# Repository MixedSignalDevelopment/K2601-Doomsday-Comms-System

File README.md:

# Doomsday Comms System (D.C.S.) — Customer Files

**SKU:** OS2601 · **Board revision:** rev B · © Mixed Signal Development GmbH

This package contains everything needed to review, fabricate, assemble, and
re-flash the Doomsday Comms System board — a two-unit personal LoRa text
messenger built on an nRF52840 (BLE) + SX1262 (LoRa 868 MHz) with a 128×64 mono
LCD, jog-wheel input, LRA haptics, piezo, and USB-C LiPo charging.

## Contents

| Folder | What's inside |
|--------|---------------|
| [`01_KiCad_Project/`](01_KiCad_Project/) | Editable source design — KiCad 7 schematic + PCB layout |
| [`02_Gerbers/`](02_Gerbers/) | Fabrication data — RS-274X gerbers + Excellon drills (4-layer) |
| [`03_BOM/`](03_BOM/) | Bill of materials (rev B) with MPNs and LCSC part numbers |
| [`04_3D_Model/`](04_3D_Model/) | Full assembly 3D model (STEP) for enclosure/mechanical fit |
| [`05_Firmware/`](05_Firmware/) | Source firmware (PlatformIO) — bring-up tester + messenger apps |

Each folder has its own `README.md` with the specifics.

## Ownership & licensing

- Design © 2026 **Mixed Signal Development GmbH**.
- **Firmware** is released under the **MIT License** — see
  [`05_Firmware/LICENSE`](05_Firmware/LICENSE).

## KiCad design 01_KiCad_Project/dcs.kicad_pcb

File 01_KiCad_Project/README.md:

# KiCad Project — Schematic & PCB

Editable source design for the Doomsday Comms System (D.C.S., SKU OS2601),
board rev B.

## Files

| File / folder | Description |
|---------------|-------------|
| `dcs.kicad_pro` | KiCad project file — open this one |
| `dcs.kicad_sch` | Schematic |
| `dcs.kicad_pcb` | PCB layout (4-layer) |
| `fp-lib-table` | Footprint-library table (project-relative, points at `Misc.pretty`) |
| `Misc.pretty/` | Bundled custom footprint library (`GSC1031YB`) |
| `3D/` | Bundled component 3D models referenced by the PCB |

## Requirements

- **KiCad 7.0 or newer** (the project was authored in KiCad 7).

Open `dcs.kicad_pro` in KiCad, then open the schematic and PCB editors from
the project window.

## Self-contained — no external libraries needed

This project has **no dependency on any machine-specific library path**. It opens
complete on a fresh KiCad install:

- **Footprints** are embedded directly in `dcs.kicad_pcb` (every placed footprint
  carries its full pad/graphics definition), so the layout opens, edits, and
  fabricates without any library at all.
- **Symbols** are cached in `dcs.kicad_sch`, so the schematic opens standalone
  too.
- The one **custom footprint library** the design uses (`GSC1031YB`) is bundled
  in `Misc.pretty/`, and `fp-lib-table` references it with the project-relative
  `${KIPRJMOD}/Misc.pretty` — so you can also place that part into new layouts.
- The per-part **3D models** are bundled in `3D/`; the PCB references them with
  the project-relative `${KIPRJMOD}/3D/…`, so the 3D viewer resolves them with no
  setup. (For a single complete model of the assembled board, the STEP in
  [`../04_3D_Model/`](../04_3D_Model/) is also provided.)

All original absolute local paths were removed — nothing points outside this
folder. The `.kicad_prl` (per-user GUI state) and editor history were not
included.

## Key components

nRF52840 module (Ebyte E73-2G4M08S1C) · SX1262 LoRa (Ai-Thinker Ra-01SH) ·
ST7565 128×64 LCD (GMG12864-06D) · DRV2605L LRA haptics · MCP73833 LiPo charger ·
TLV75533 LDO · TM-1011A jog wheel.

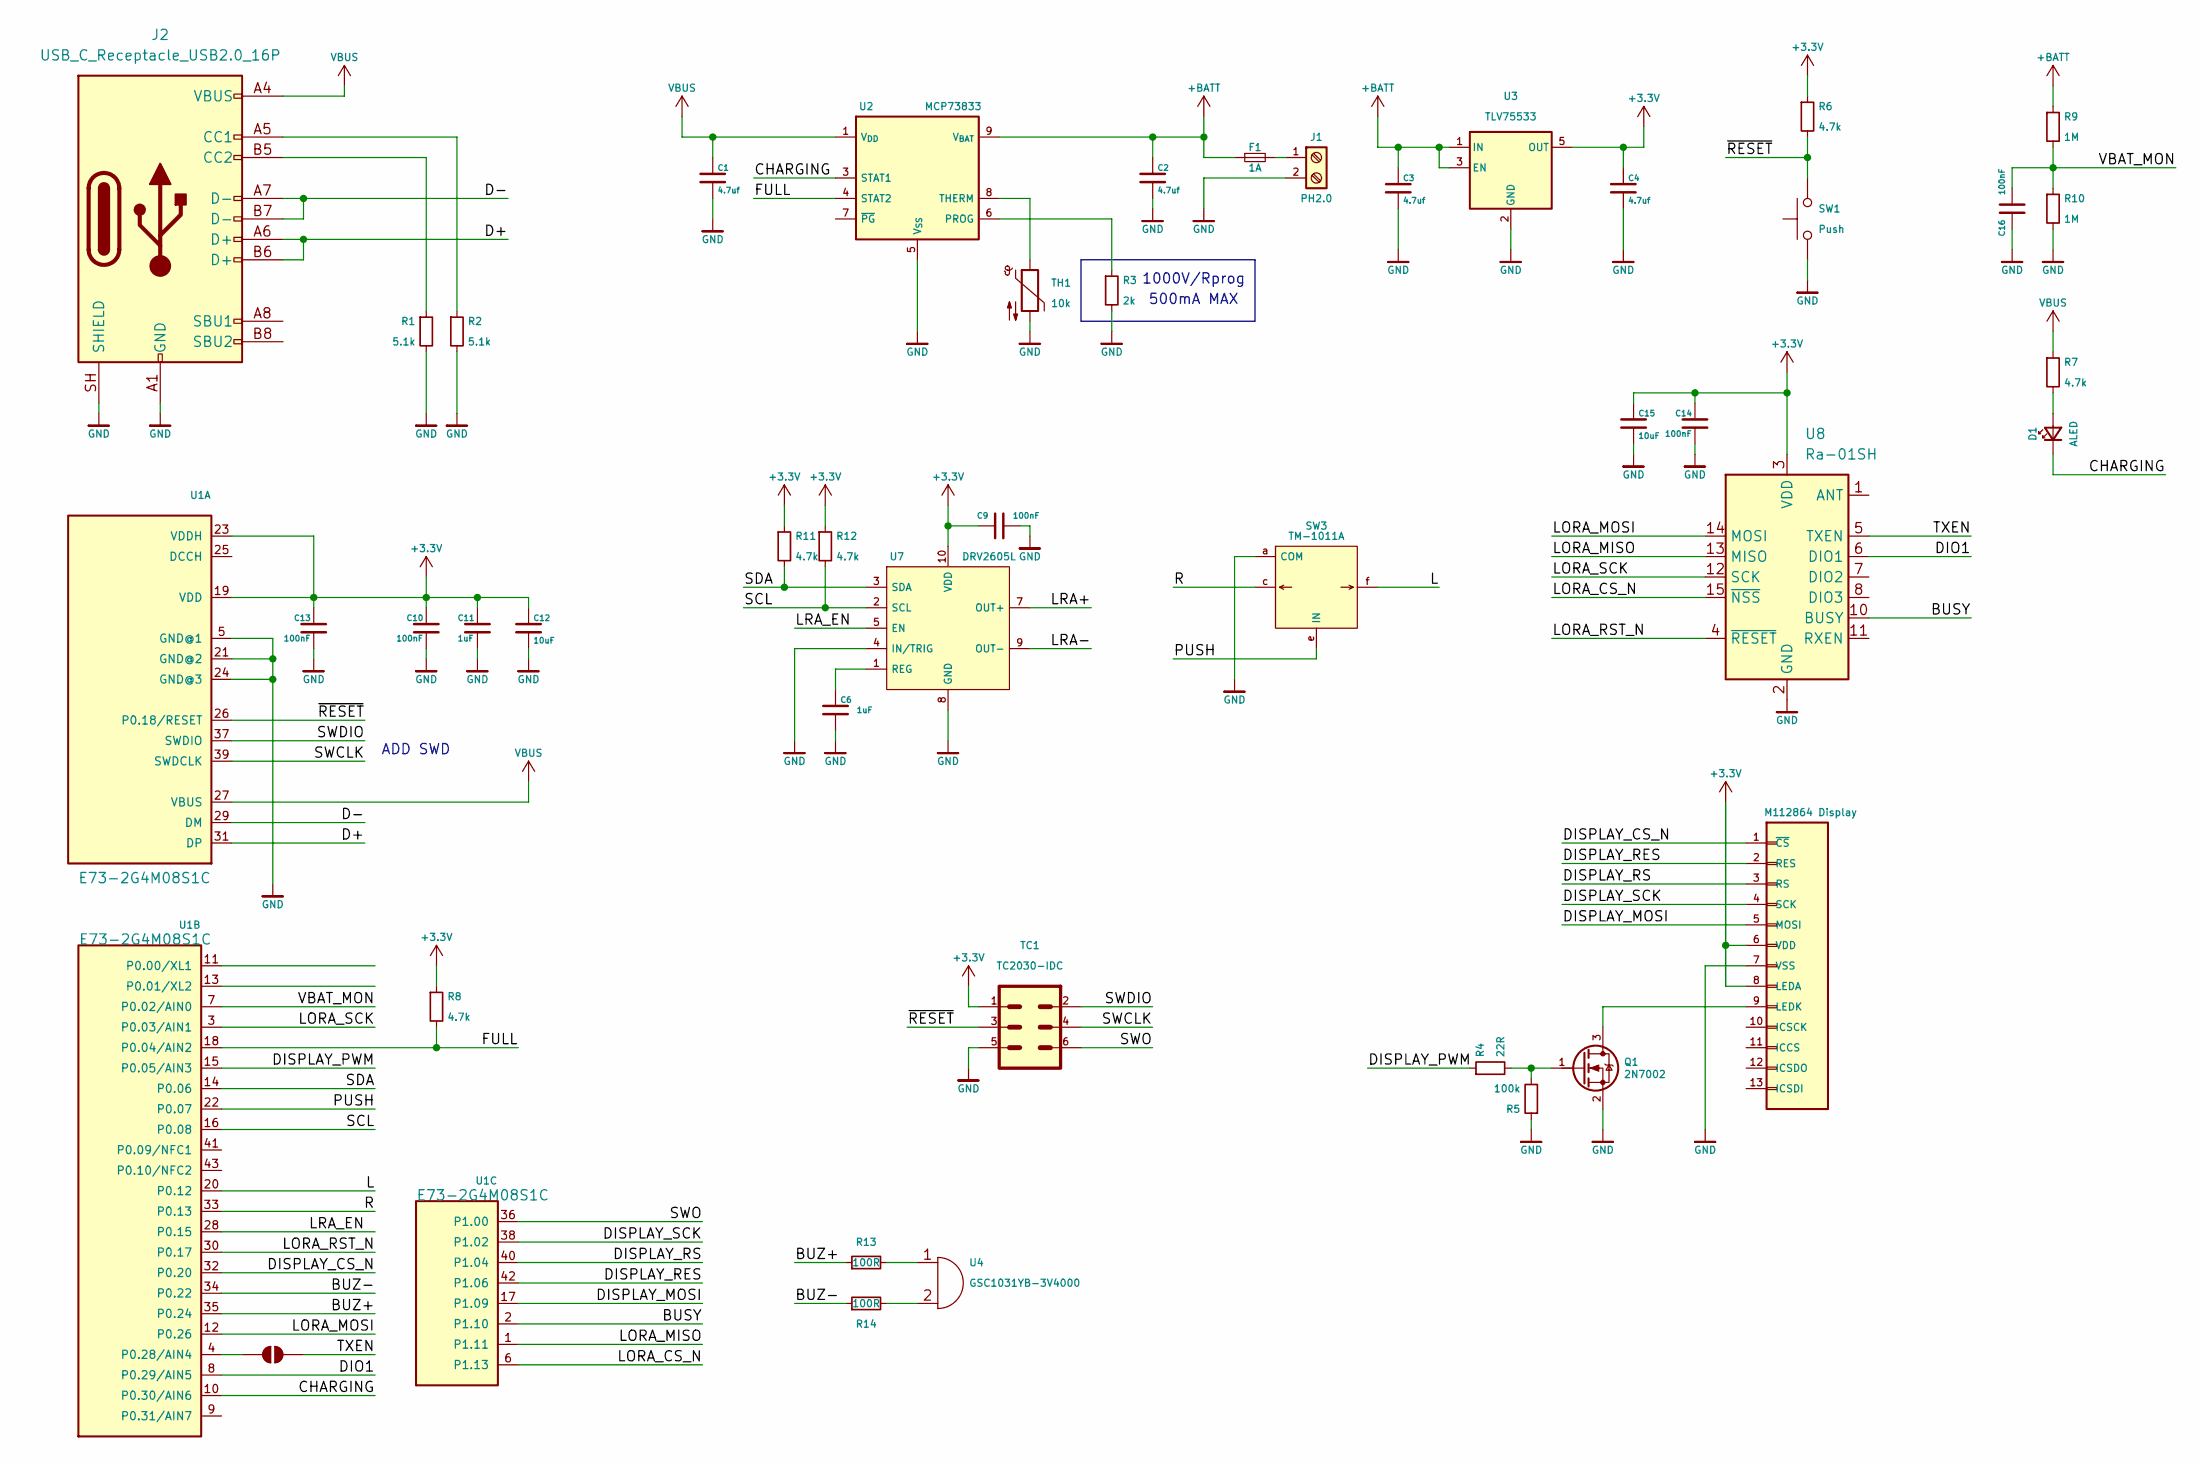
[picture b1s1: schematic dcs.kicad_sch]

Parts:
C1, C2, C3, C4: 4.7uf; C_0805; MPN CL21A475KAQNNNE; LCSC OC C354262
C6, C11: 1uF; C_0805; MPN CC0805KKX7R7BB105; LCSC OC C91186
C9, C10, C13, C14, C16: 100nF; C_0805; MPN CC0805KRX7R9BB104; LCSC OC C396718
C12, C15: 10uF; C_0805; MPN CL21B106KOQNNNE
D1: ALED; SideLED_4x1.4mm; MPN XL-4008SURC; LCSC OC C2843771
F1: 1A; R_0603; MPN JB06F1001R
J1: PH2.0; JST_PH_S2B-PH-SM4-TB_1x02-1MP_P2.00mm_Horizontal; LCSC OC C295747
J2: USB_C_Receptacle_USB2.0_16P; USB_C_16P_Horizontal; MPN TYPE-C 16PIN 2MD(073); LCSC OC C2765186
JP1: SolderJumper_2; SolderJumper-2_P1.3mm_Open_RoundedPad1.0x1.5mm
M1: 12864 Display; 12864DisplayModule
Q1: 2N7002; SOT-23; LCSC OC C916396
R1, R2: 5.1k; R_0805; MPN RC0805FR-075K1L; LCSC OC C84375
R3: 2k; R_0805; MPN RC0805JR-072KL; LCSC OC C114748
R4: 22R; R_0805; MPN RC0805FR-0722RL; LCSC OC C107702
R5: 100k; R_0805; MPN RC0805FR-07100KL; LCSC OC C96346
R6, R7, R8, R11, R12: 4.7k; R_0805; MPN RC0402FR-074K7L; LCSC OC C60816
R9, R10: 1M; R_0805; MPN RC0805FR-071ML; LCSC OC C706228
R13, R14: 100R; R_0805; MPN RC0805FR-07100RL; LCSC OC C105577
SW1: Push; SideSwitch; MPN MPTCLG-Q-T/R; LCSC OC C240296
SW3: TM-1011A; SlideKnob; MPN TM-1011A; LCSC OC C318960
TC1: TC2030-IDC
TH1: 10k; R_0603; MPN NTCG164BH103HT1; LCSC OC C415353
U1: E73-2G4M08S1C; MPN E73-2G4M08S1C; LCSC OC C356849
U2: MCP73833; MSOP-10_3x3mm_P0.5mm; MPN MCP73833T-AMI/UN
U3: TLV75533; SOT-23-5; MPN TLV75533PDYDR; LCSC OC C28642215
U4: GSC1031YB-3V4000; GSC1031YB; MPN GSC1031YB-3V4000; LCSC OC C255331
U7: DRV2605L; MSOP-10_3x3mm_P0.5mm; MPN DRV2605LDGSR; LCSC OC C527464
U8: Ra-01SH; Ai-Thinker-Ra-01-LoRa; MPN Ra-01SH; LCSC OC C2764087

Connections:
+3.3V: C4.1, C9.1, C10.1, C11.1, C12.1, C13.1, C14.1, C15.1, M1.6 (VDD), M1.8 (LEDA), R6.1, R8.1, R11.1, R12.1, TC1.1, U1.19 (VDD), U1.23 (VDDH), U3.5 (OUT), U7.6 (VDD/NC), U7.10 (VDD), U8.3 (VDD)
+BATT: C2.1, C3.1, F1.1, R9.1, U2.9 (V_{BAT}), U2.10 (V_{BAT}), U3.1 (IN), U3.3 (EN)
/BUSY: U1.2 (P1.10), U8.10 (BUSY)
/BUZ+: R13.1, U1.35 (P0.24)
/BUZ-: R14.1, U1.34 (P0.22)
/CHARGING: D1.C, U1.10 (P0.30/AIN6), U2.3 (STAT1)
/D+: J2.A6 (D+), J2.B6 (D+), U1.31 (DP)
/D-: J2.A7 (D-), J2.B7 (D-), U1.29 (DM)
/DIO1: U1.8 (P0.29/AIN5), U8.6 (DIO1)
/DISPLAY_CS_N: M1.1 (~CS), U1.32 (P0.20)
/DISPLAY_MOSI: M1.5 (MOSI), U1.17 (P1.09)
/DISPLAY_PWM: R4.1, U1.15 (P0.05/AIN3)
/DISPLAY_RES: M1.2 (RES), U1.42 (P1.06)
/DISPLAY_RS: M1.3 (RS), U1.40 (P1.04)
/DISPLAY_SCK: M1.4 (SCK), U1.38 (P1.02)
/FULL: R8.2, U1.18 (P0.04/AIN2), U2.4 (STAT2)
/L: SW3.f, SW3.g, U1.20 (P0.12)
/LORA_CS_N: U1.6 (P1.13), U8.15 (~NSS)
/LORA_MISO: U1.1 (P1.11), U8.13 (MISO)
/LORA_MOSI: U1.12 (P0.26), U8.14 (MOSI)
/LORA_RST_N: U1.30 (P0.17), U8.4 (~RESET)
/LORA_SCK: U1.3 (P0.03/AIN1), U8.12 (SCK)
/LRA+: U7.7 (OUT+)
/LRA-: U7.9 (OUT-)
/LRA_EN: U1.28 (P0.15), U7.5 (EN)
/PUSH: SW3.e (IN), U1.22 (P0.07)
/R: SW3.c, SW3.d, U1.33 (P0.13)
/SCL: R12.2, U1.16 (P0.08), U7.2 (SCL)
/SDA: R11.2, U1.14 (P0.06), U7.3 (SDA)
/SWCLK: TC1.4, U1.39 (SWDCLK)
/SWDIO: TC1.2, U1.37 (SWDIO)
/SWO: TC1.6, U1.36 (P1.00)
/TXEN: JP1.2 (B), U8.5 (TXEN)
/VBAT_MON: C16.2, R9.2, R10.1, U1.7 (P0.02/AIN0)
/~RESET: R6.2, SW1.2, TC1.3, U1.26 (P0.18/RESET)
GND: C1.2, C2.2, C3.2, C4.2, C6.2, C9.2, C10.2, C11.2, C12.2, C13.2, C14.2, C15.2, C16.1, J1.2, J2.A1 (GND), J2.A12 (GND), J2.B1 (GND), J2.B12 (GND), J2.SH (SHIELD), M1.7 (VSS), Q1.2 (S), R1.2, R2.2, R3.2, R5.1, R10.2, SW1.1, SW3.a (COM), SW3.b (COM), TC1.5, TH1.2, U1.5 (GND@1), U1.21 (GND@2), U1.24 (GND@3), U2.5 (V_{SS}), U3.2 (GND), U7.4 (IN/TRIG), U7.8 (GND), U8.2 (GND), U8.9 (GND), U8.16 (GND)
unnamed: D1.A, R7.2
unnamed: F1.2, J1.1
unnamed: J2.A5 (CC1), R2.1
unnamed: J2.B5 (CC2), R1.1
unnamed: JP1.1 (A), U1.4 (P0.28/AIN4)
unnamed: M1.9 (LEDK), Q1.3 (D)
unnamed: Q1.1 (G), R4.2, R5.2
unnamed: R13.2, U4.1
unnamed: R14.2, U4.2
unnamed: R3.1, U2.6 (PROG)
unnamed: TH1.1, U2.8 (THERM)
unnamed: C6.1, U7.1 (REG)
VBUS: C1.1, J2.A4 (VBUS), J2.A9 (VBUS), J2.B4 (VBUS), J2.B9 (VBUS), R7.1, U1.27 (VBUS), U2.1 (V_{DD}), U2.2 (V_{DD})

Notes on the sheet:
1000V/Rprog
ADD SWD
500mA MAX

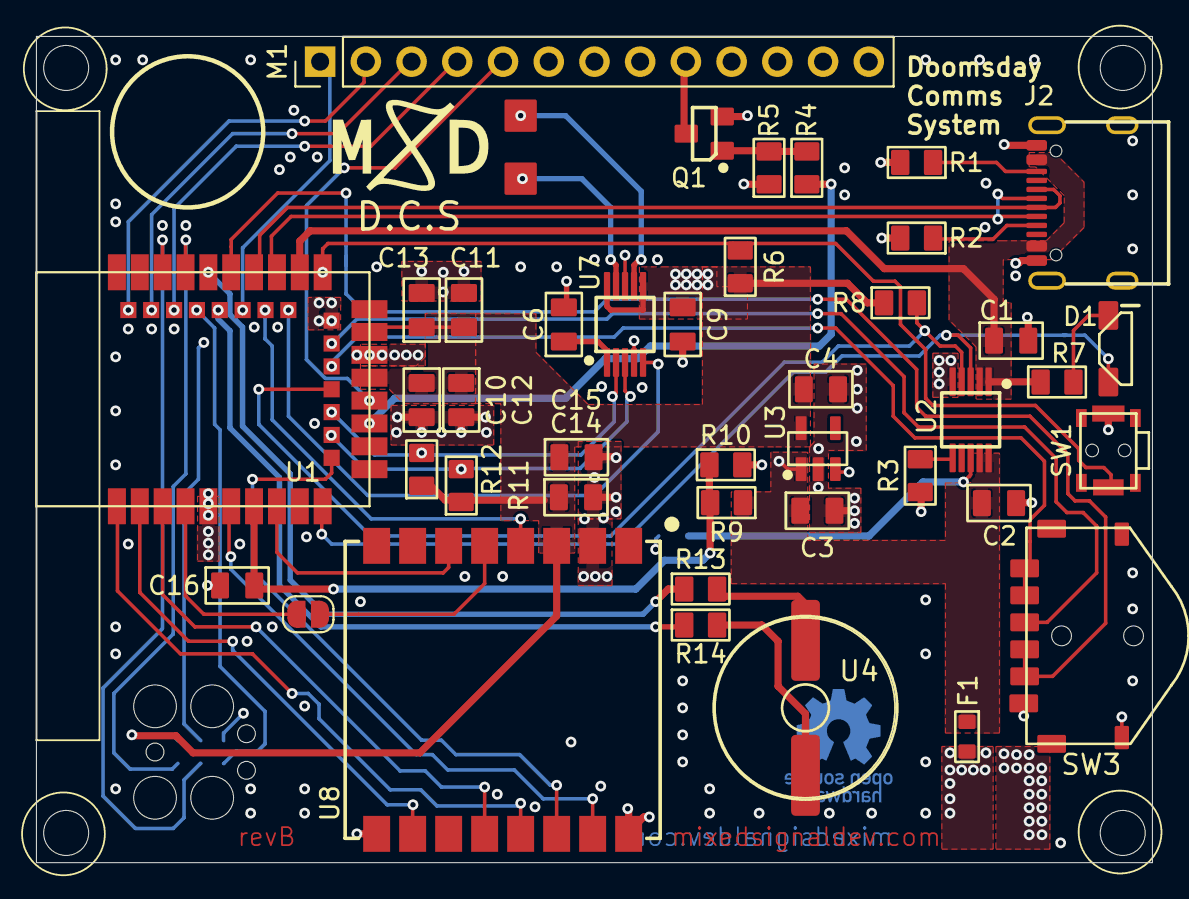
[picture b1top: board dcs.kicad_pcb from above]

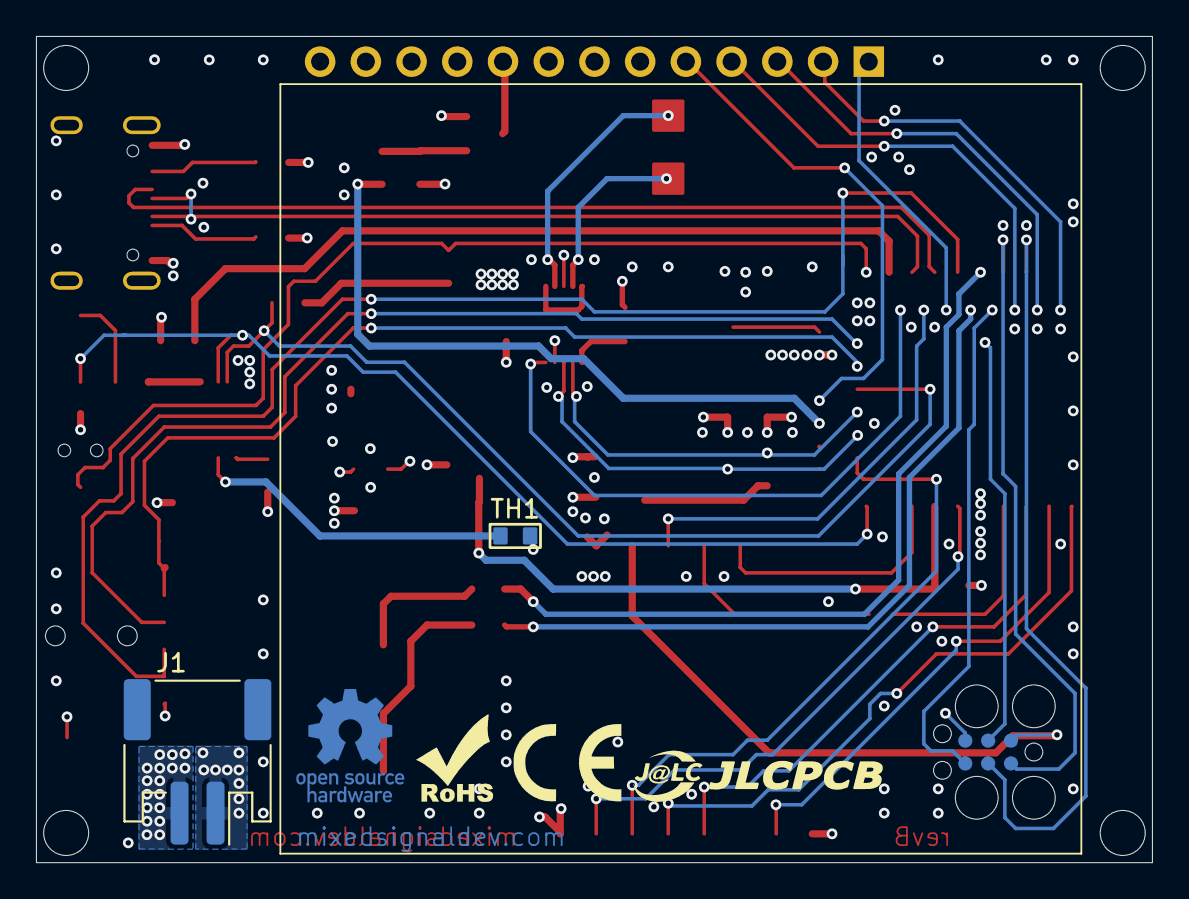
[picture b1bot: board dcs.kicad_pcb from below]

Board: 4 copper layers, 62.0 x 45.9 mm, 44 parts (3 on the bottom side), 47 nets.

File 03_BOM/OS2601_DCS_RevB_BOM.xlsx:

OS-K2601 Messager — Bill of Materials
Rev B · nRF52 BLE + LoRa · USB-C LiPo charging · 27 line items · 44 components
Placed | Designators | Value | Package | Qty | MPN | LCSC OC | Notes
1 · SMD passives (0805 / 0603) flattest parts first
☐ | C1–C4 | 4.7µF | 0805 | 4 | CL21A475KAQNNNE | C354262
☐ | C6, C11 | 1µF | 0805 | 2 | CC0805KKX7R7BB105 | C91186
☐ | C9, C10, C13, C14, C16 | 100nF | 0805 | 5 | CC0805KRX7R9BB104 | C396718
☐ | C12, C15 | 10µF | 0805 | 2 | CL21B106KOQNNNE | C95841 | No LCSC # — order by MPN
☐ | R1, R2 | 5.1k | 0805 | 2 | RC0805FR-075K1L | C84375
☐ | R3 | 2k | 0805 | 1 | RC0805JR-072KL | C114748
☐ | R4 | 22R | 0805 | 1 | RC0805FR-0722RL | C107702
☐ | R5 | 100k | 0805 | 1 | RC0805FR-07100KL | C96346
☐ | R6–R8, R11, R12, R15 | 4.7k | 0805 | 6 | RC0805FR-074K7L | C60816
☐ | R9, R10 | 1M | 0805 | 2 | RC0805FR-071ML | C706228
☐ | R13, R14 | 100R | 0805 | 2 | RC0805FR-07100RL | C105577 | Alt LCSC: C2907218
☐ | F1 | 1A fuse | 0603 | 1 | JB06F1001R | C151139 | No LCSC # — order by MPN
☐ | TH1 | 10k NTC | 0603 | 1 | NTCG164BH103HT1 | C415353
2 · SMD ICs & transistor use flux — mind pin 1
☐ | Q1 | 2N7002 | SOT-23 | 1 |  | C916396
☐ | U2 | MCP73833 | MSOP-10 | 1 | MCP73833T-AMI/UN |  | Mind pin 1 · no LCSC #, cheaper on Digikey
☐ | U3 | TLV75533 | SOT-23-5 | 1 | TLV75533PDYDR | C28642215
☐ | U7 | DRV2605L | MSOP-10 | 1 | DRV2605LDGSR | C527464 | Mind pin 1
3 · LED & switches LED is directional
☐ | D1 | Side LED | 4×1.4mm | 1 | XL-4008SURC | C2843771 | Polarity — check cathode mark
☐ | SW1 | Push button | Side SMD | 1 | MPTCLG-Q-T/R | C240296
☐ | SW3 | Slide switch | TM-1011A | 1 | TM-1011A | C318960
4 · Modules & sounder keep antennas clear of solder
☐ | U1 | E73-2G4M08S1C | SMD module | 1 | E73-2G4M08S1C | C356849 | nRF52 BLE
☐ | U8 | Ra-01SH | SMD module | 1 | Ra-01SH | C2764087 | LoRa
☐ | U4 | GSC1031YB-3V4000 | SMD buzzer | 1 | GSC1031YB-3V4000 | C255331
☐ |  | Antenna |  | 1 | ANT-868-CW-HD-SMA | Link
☐ |  | VG0832012 | LRA | 1 | VG0832012 | Link
☐ | M1 | 12864 display | Module | 1 | 12864-06D | Link
5 · Connectors & programming last — the tall parts
☐ | J1 | PH2.0 battery | JST SMD | 1 |  | C295747 | Check battery polarity
☐ | J2 | USB-C 16P | USB-C SMD | 1 | TYPE-C 16PIN 2MD(073) | C2765186
☐ | TC1 | TC2030-IDC | Tag-Connect | 1 |  |  | Pads only — no part fitted
☐ → pick ☑ from the dropdown (or tick on paper) as you place each part. Solder 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

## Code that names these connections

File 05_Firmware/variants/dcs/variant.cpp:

/* ===========================================================================
 *  SPDX-License-Identifier: MIT
 *  Copyright (c) 2026 Mixed Signal Development GmbH
 *
 *  Doomsday Comms System (D.C.S., SKU OS2601) rev-A — Arduino board variant
 *  implementation
 *
 *  g_ADigitalPinMap[] maps Arduino index -> nRF absolute pin (32*port + pin).
 *  The order here MUST match the PIN_* indices in variant.h.
 *
 *  Also instantiates the default Wire (I2C) and SPI (LoRa) bus objects on the
 *  correct nRF pins, as the Adafruit nRF52 core expects the variant to do.
 * =========================================================================== */
#include "variant.h"
#include "wiring_constants.h"
#include "wiring_digital.h"
#include "nrf.h"

const uint32_t g_ADigitalPinMap[PINS_COUNT] =
{
     2,   /* [0]  PIN_VBAT_MON     P0.02 / AIN0 */
     3,   /* [1]  PIN_LORA_SCK     P0.03 */
     4,   /* [2]  PIN_FULL         P0.04 */
     5,   /* [3]  PIN_DISPLAY_PWM  P0.05 */
     6,   /* [4]  PIN_SDA          P0.06 */
     7,   /* [5]  PIN_PUSH         P0.07 */
     8,   /* [6]  PIN_SCL          P0.08 */
    12,   /* [7]  PIN_WHEEL_R      P0.12 */
    13,   /* [8]  PIN_WHEEL_L      P0.13 */
    15,   /* [9]  PIN_LRA_EN       P0.15 */
    17,   /* [10] PIN_LORA_RST_N   P0.17 */
    20,   /* [11] PIN_DISPLAY_CS_N P0.20 */
    22,   /* [12] PIN_BUZ_MINUS    P0.22 */
    24,   /* [13] PIN_BUZ_PLUS     P0.24 */
    26,   /* [14] PIN_LORA_MOSI    P0.26 */
    28,   /* [15] PIN_TXEN         P0.28  <-- NEVER drive as output */
    29,   /* [16] PIN_DIO1         P0.29 */
    30,   /* [17] PIN_CHARGING     P0.30 */
    32,   /* [18] PIN_SWO          P1.00  reserved */
    34,   /* [19] PIN_DISPLAY_SCK  P1.02 */
    36,   /* [20] PIN_DISPLAY_RS   P1.04 */
    38,   /* [21] PIN_DISPLAY_RES  P1.06 */
    41,   /* [22] PIN_DISPLAY_MOSI P1.09 */
    42,   /* [23] PIN_BUSY         P1.10 */
    43,   /* [24] PIN_LORA_MISO    P1.11 */
    45,   /* [25] PIN_LORA_CS_N    P1.13 */
     9,   /* [26] PIN_SERIAL1_RX   P0.09  NFC1, unused placeholder */
    10,   /* [27] PIN_SERIAL1_TX   P0.10  NFC2, unused placeholder */
};

/* NOTE: the default Wire (I2C) and SPI (LoRa) bus objects are NOT defined here.
 * PlatformIO's bundled Wire/SPI libraries already instantiate them using this
 * variant's PIN_WIRE_SDA/SCL and PIN_SPI_* macros, so defining them again
 * would be a duplicate-symbol link error. The pin map below is all we own. */

void initVariant(void)
{
    /* Nothing forced high at boot. The backlight FET has a hardware pulldown
     * so the screen powers up dark until firmware asks for it. We deliberately
     * leave TXEN (P0.28) completely untouched — it is a module output. */
}
